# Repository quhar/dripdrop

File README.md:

# dripdrop
ESPHome based node to manage irigation, garage doors and more!

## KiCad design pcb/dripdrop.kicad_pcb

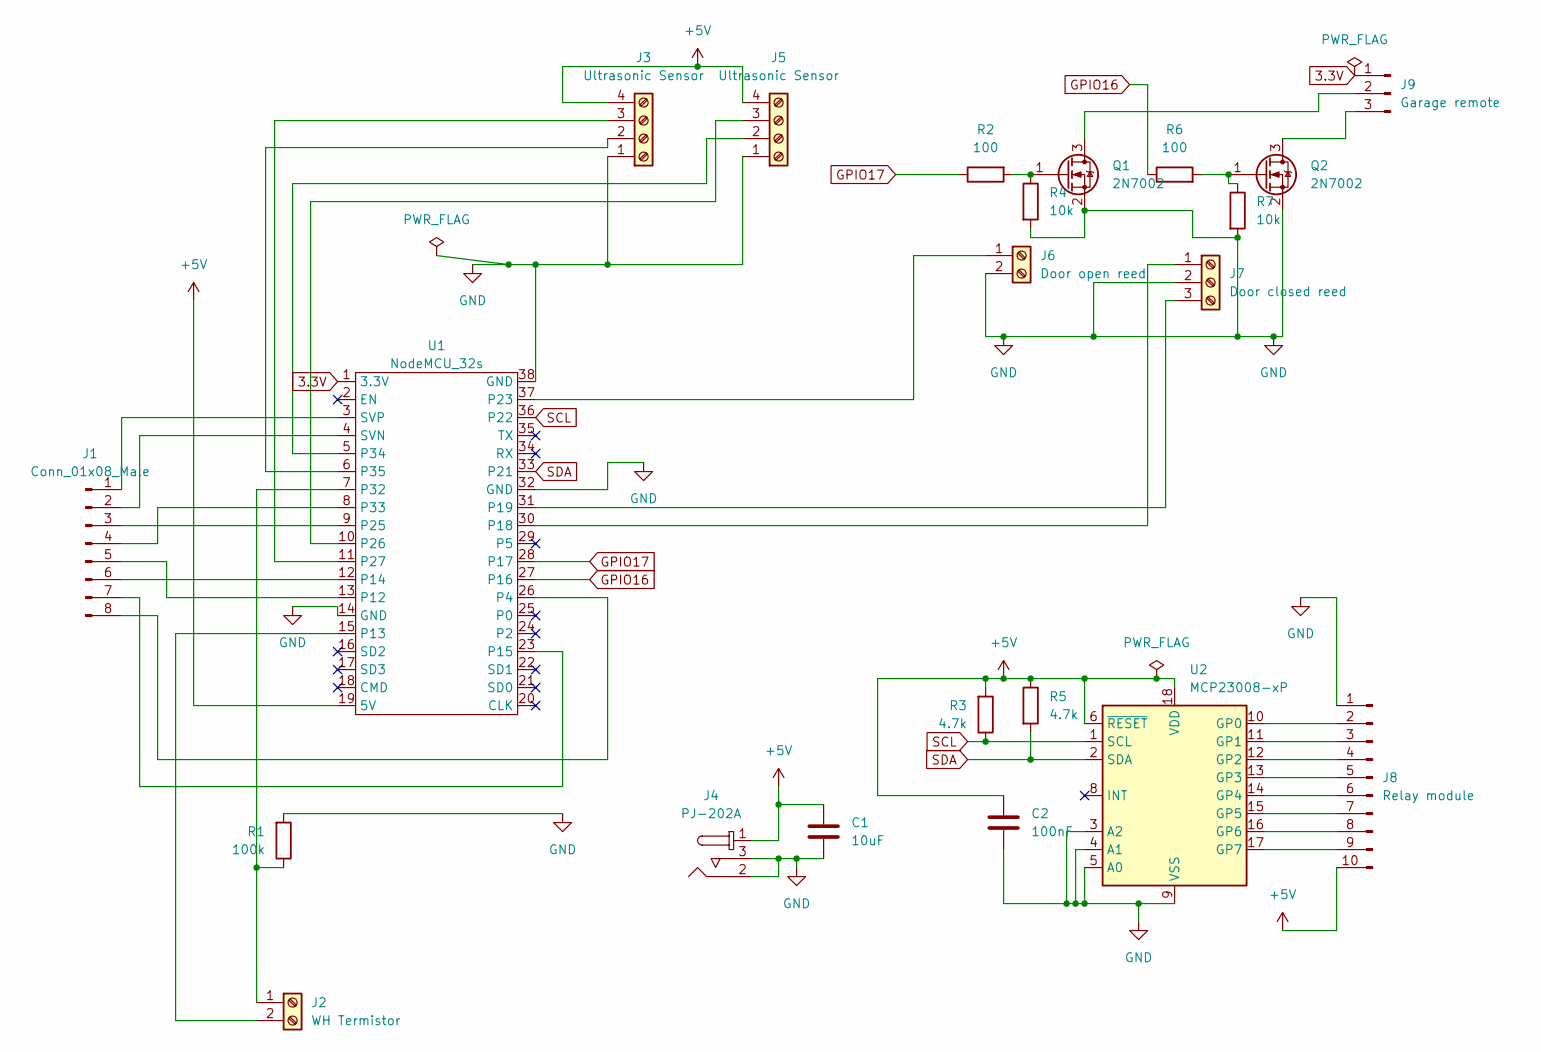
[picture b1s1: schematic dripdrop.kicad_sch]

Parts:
C1: 10uF; C_1206_3216Metric_Pad1.33x1.80mm_HandSolder
C2: 100nF; C_0805_2012Metric_Pad1.18x1.45mm_HandSolder
J1: Conn_01x08_Male; PinHeader_2x04_P2.54mm_Vertical
J2: WH Termistor; TerminalBlock_Phoenix_MPT-0,5-2-2.54_1x02_P2.54mm_Horizontal
J3, J5: Ultrasonic Sensor; TerminalBlock_Phoenix_MPT-0,5-4-2.54_1x04_P2.54mm_Horizontal
J4: PJ-202A; Barrel_Jack_5.5mmODx2.1mmID_PJ-102A; MPN PJ-202A; Digi-Key_PN CP-202A-ND
J6: Door open reed; TerminalBlock_Phoenix_MPT-0,5-2-2.54_1x02_P2.54mm_Horizontal
J7: Door closed reed; TerminalBlock_Phoenix_MPT-0,5-3-2.54_1x03_P2.54mm_Horizontal
J8: Relay module; PinHeader_1x10_P2.54mm_Vertical
J9: Garage remote; PinSocket_1x03_P2.54mm_Vertical
Q1, Q2: 2N7002; SOT-323_SC-70_Handsoldering
R1: 100k; R_0805_2012Metric
R2, R6: 100; R_0805_2012Metric
R3, R5: 4.7k; R_0805_2012Metric
R4, R7: 10k; R_0805_2012Metric
U1: NodeMCU_32s; NodeMCU 32S
U2: MCP23008-xP; DIP-18_W7.62mm

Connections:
3.3V: J9.1, U1.1 (3.3V)
+5V: C1.1, C2.1, J3.4, J4.1, J5.4, J8.10, R3.2, R5.1, U1.19 (5V), U2.6 (~RESET), U2.18 (VDD)
GND: C1.2, C2.2, J3.1, J4.2, J4.3, J5.1, J6.2, J7.2, J8.1, Q1.2 (S), Q2.2 (S), R1.2, R4.2, R7.2, U1.14 (GND), U1.32 (GND), U1.38 (GND), U2.3 (A2), U2.4 (A1), U2.5 (A0), U2.9 (VSS)
GPIO16: R6.1, U1.27 (P16)
GPIO17: R2.1, U1.28 (P17)
unnamed: J1.1, U1.3 (SVP)
unnamed: J1.2, U1.4 (SVN)
unnamed: J1.3, U1.9 (P25)
unnamed: J1.4, U1.8 (P33)
unnamed: J1.5, U1.13 (P12)
unnamed: J1.6, U1.12 (P14)
unnamed: J1.7, U1.23 (P15)
unnamed: J1.8, U1.26 (P4)
unnamed: J2.1, R1.1, U1.7 (P32)
unnamed: J2.2, U1.15 (P13)
unnamed: J3.2, U1.6 (P35)
unnamed: J3.3, U1.11 (P27)
unnamed: J6.1, U1.37 (P23)
unnamed: J7.1, U1.30 (P18)
unnamed: J7.3, U1.31 (P19)
unnamed: J8.2, U2.10 (GP0)
unnamed: J8.3, U2.11 (GP1)
unnamed: J8.4, U2.12 (GP2)
unnamed: J8.5, U2.13 (GP3)
unnamed: J8.6, U2.14 (GP4)
unnamed: J8.7, U2.15 (GP5)
unnamed: J8.8, U2.16 (GP6)
unnamed: J8.9, U2.17 (GP7)
unnamed: J9.2, Q1.3 (D)
unnamed: J9.3, Q2.3 (D)
unnamed: Q1.1 (G), R2.2, R4.1
unnamed: Q2.1 (G), R6.2, R7.1
unnamed: J5.2, U1.5 (P34)
unnamed: J5.3, U1.10 (P26)
SCL: R3.1, U1.36 (P22), U2.1 (SCL)
SDA: R5.2, U1.33 (P21), U2.2 (SDA)

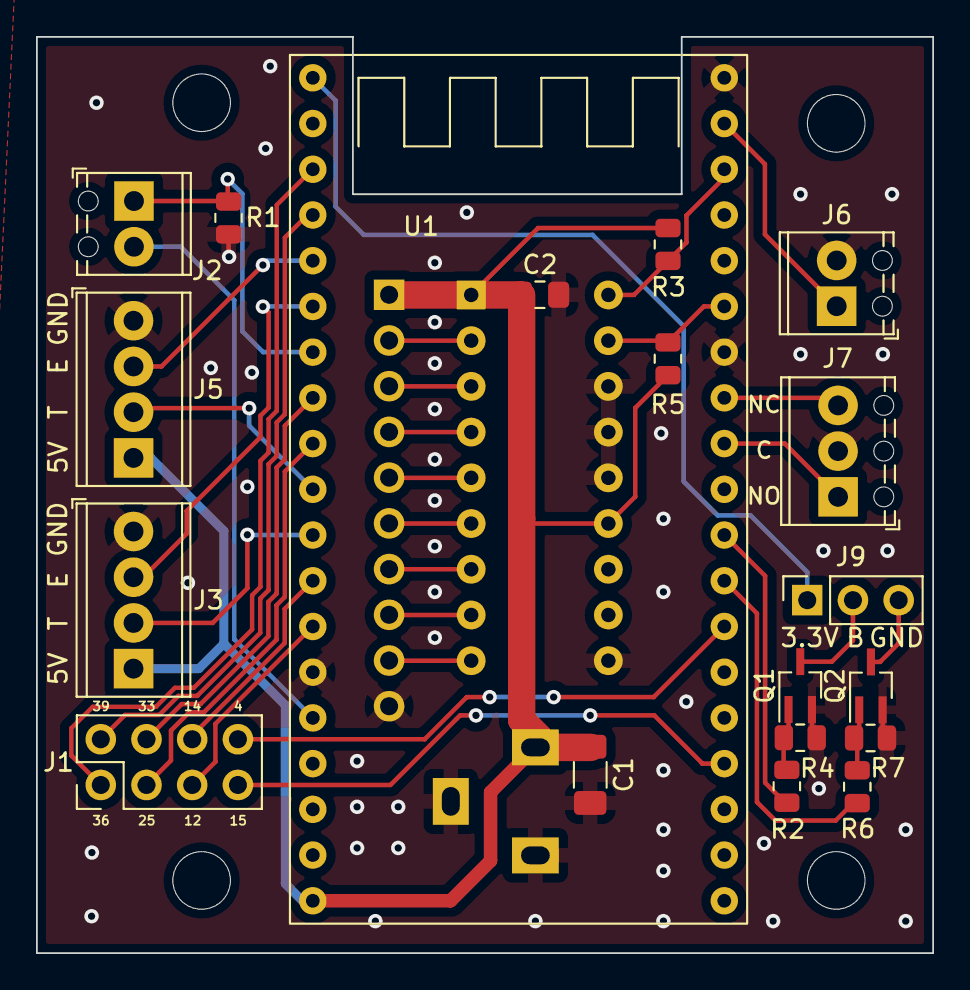
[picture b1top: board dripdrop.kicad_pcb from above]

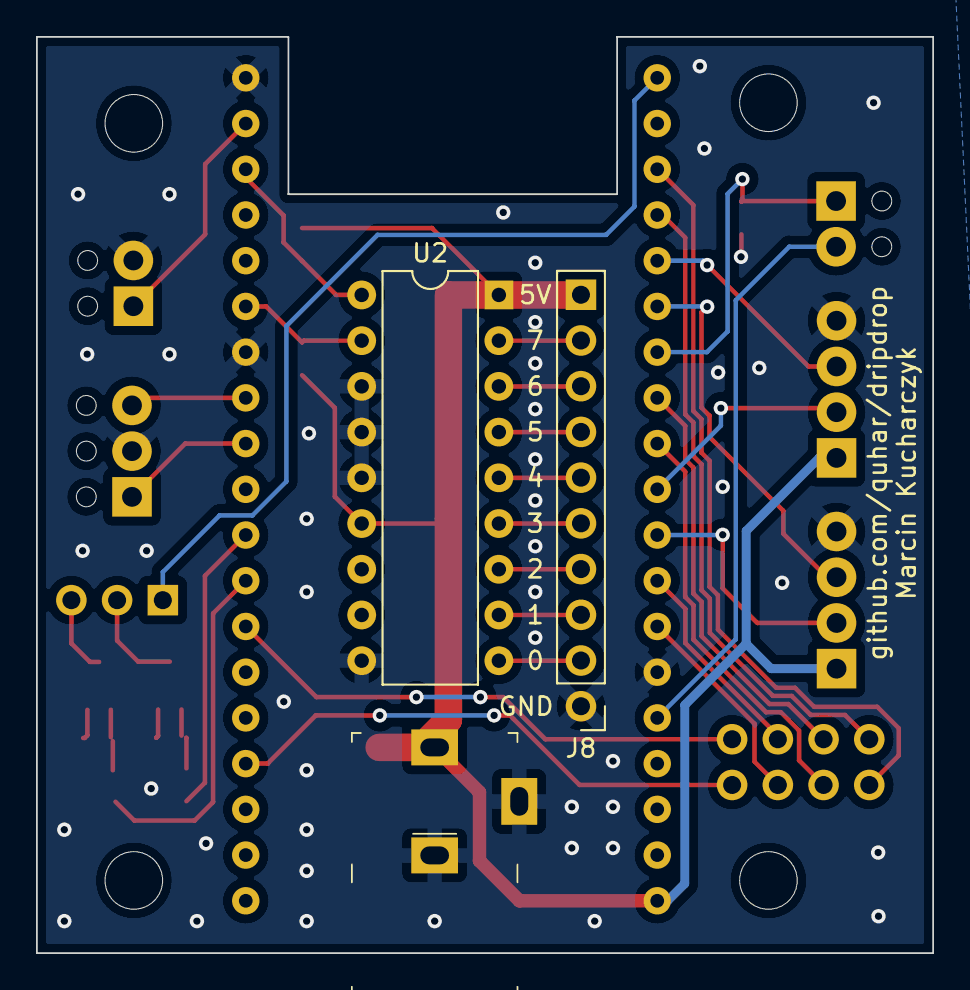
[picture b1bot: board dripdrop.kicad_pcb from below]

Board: 2 copper layers, 49.8 x 50.9 mm, 22 parts (3 on the bottom side), 36 nets.

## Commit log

2022-07-09 First PCB revision
